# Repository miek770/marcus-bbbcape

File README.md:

# marcus-bbbcape

Beaglebone Black cape for my robot, see:

- [marcus-base](https://github.com/miek770/marcus-base)
- [marcus-boucliers](https://github.com/miek770/marcus-boucliers)

The general goal is to reduce the amount of loose wires on the robot and the required space. The current platform is not compact at all, and adding more stuff (ex.: cannon, turrent, shields) seems like quite the challenge.

Ideally I would use Molex connectors but it would probably eat up too much space. I would like to keep the PCB as small as possible, mostly to keep the cost down. Right-angle headers would work as well, but I think I'll quickly run out of borders. Perhaps right-angle headers for stuff going down, and straight headers for stuff going up?

The cape should be stackable, which means that P8 and P9 should be female headers with long leads. The alternative would be male headers mounted on the bottom. Then again, with plenty of headers going up I probably won't be able to put another cape on top anyways. Still, having female headers allows me to add wires in the future for unplanned expansions.

## 1. To do list

- Add UART2;
- Add battery voltage monitoring (remember the 1.8V analog input limitation);
- Move the top headers' titles below them, otherwise they will be hidden by the right-angle headers I plan on using;
- Correct title, it's partially hidden by the P9 header;
- Output 6.5V somewhere other than for the camera. Some other system may very well need it;
- I don't like how the rangefinders' pins are mirrored, but I've added indications. If it's not too complicated I'd like to mirror 2 of them;
- Add an LED tied to an unused pin, for testing purposes;
- Double-check the big capacitor polarity. I would've thought the square pad to be for the negative pin, but the top silk screen says otherwise;
- Add headers 1st pin markers on all of them and resize the existing 1's (not existing ones but existing 1's);
- Document pins usage. Just need to integrate this info in marcus-base/modules/pins.py which holds a dictionary of pins usage.

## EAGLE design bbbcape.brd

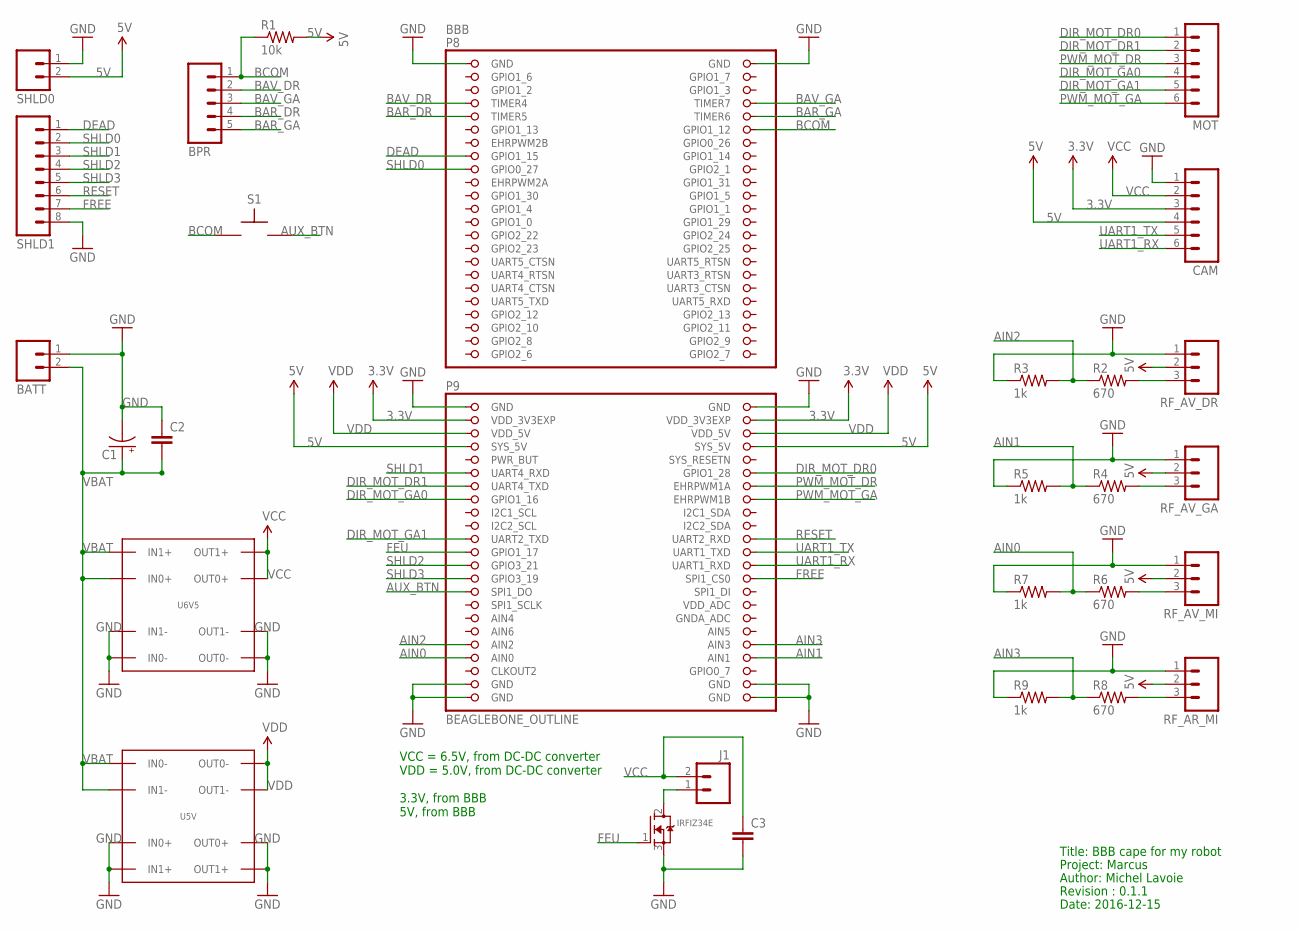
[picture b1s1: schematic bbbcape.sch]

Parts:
BATT: M02PTH; 1X02
BBB: BEAGLEBONE_OUTLINE; BEAGLEBONE_SHIELD
BPR: M05PTH; 1X05
C1: 100UF-25V-20%(PTH); CPOL-RADIAL-100UF-25V
C2, C3: 0.1UF-50V-20%(PTH)KIT-EZ; CAP-PTH-SMALL-KIT
CAM: M06SILK_FEMALE_PTH; 1X06
IRFIZ34E: MOSFET-NGDS_TO220V; TO220V
J1: M02PTH; 1X02
MOT: M06SILK_FEMALE_PTH; 1X06
R1: 10k; AXIAL-0.3
R2, R4, R6, R8: 670; AXIAL-0.3
R3, R5, R7, R9: 1k; AXIAL-0.3
RF_AR_MI: M03PTH; 1X03
RF_AV_DR: M03PTH; 1X03
RF_AV_GA: M03PTH; 1X03
RF_AV_MI: M03PTH; 1X03
S1: TACTILE-SPST-6MM-SLIM; 6MM-SLIM
SHLD0: M02PTH; 1X02
SHLD1: M08; 1X08_ROUND
U5V, U6V5: SEEED-MP1584

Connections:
3.3V: BBB.49 (VDD_3V3EXP), BBB.50 (VDD_3V3EXP), CAM.3
5V: BBB.53 (SYS_5V), BBB.54 (SYS_5V), CAM.4, R1.P$2 (2), RF_AR_MI.2, RF_AV_DR.2, RF_AV_GA.2, RF_AV_MI.2, SHLD0.2
AIN0: BBB.85 (AIN0), R6.P$1 (1), R7.P$2 (2)
AIN1: BBB.86 (AIN1), R4.P$1 (1), R5.P$2 (2)
AIN2: BBB.83 (AIN2), R2.P$1 (1), R3.P$2 (2)
AIN3: BBB.84 (AIN3), R8.P$1 (1), R9.P$2 (2)
AUX_BTN: BBB.75 (SPI1_DO), S1.P$2
BAR_DR: BBB.9 (TIMER5), BPR.4
BAR_GA: BBB.10 (TIMER6), BPR.5
BAV_DR: BBB.7 (TIMER4), BPR.2
BAV_GA: BBB.8 (TIMER7), BPR.3
BCOM: BBB.12 (GPIO1_12), BPR.1, R1.P$1 (1), S1.P$1
DEAD: BBB.15 (GPIO1_15), SHLD1.1
DIR_MOT_DR0: BBB.58 (GPIO1_28), MOT.1
DIR_MOT_DR1: BBB.59 (UART4_TXD), MOT.2
DIR_MOT_GA0: BBB.61 (GPIO1_16), MOT.4
DIR_MOT_GA1: BBB.67 (UART2_TXD), MOT.5
FEU: BBB.69 (GPIO1_17), IRFIZ34E.1 (G)
FREE: BBB.74 (SPI1_CS0), SHLD1.7
GND: BATT.1, BBB.1 (GND), BBB.2 (GND), BBB.47 (GND), BBB.48 (GND), BBB.89 (GND), BBB.90 (GND), BBB.91 (GND), BBB.92 (GND), C1.2 (-), C2.1, C3.2, CAM.1, IRFIZ34E.3 (S), R3.P$1 (1), R5.P$1 (1), R7.P$1 (1), R9.P$1 (1), RF_AR_MI.1, RF_AV_DR.1, RF_AV_GA.1, RF_AV_MI.1, SHLD0.1, SHLD1.8, U5V.IN0+, U5V.IN1+, U5V.OUT0+, U5V.OUT1+, U6V5.IN0-, U6V5.IN1-, U6V5.OUT0-, U6V5.OUT1-
unnamed: R2.P$2 (2), RF_AV_DR.3
unnamed: R4.P$2 (2), RF_AV_GA.3
unnamed: IRFIZ34E.2 (D), J1.1
unnamed: R6.P$2 (2), RF_AV_MI.3
unnamed: R8.P$2 (2), RF_AR_MI.3
PWM_MOT_DR: BBB.60 (EHRPWM1A), MOT.3
PWM_MOT_GA: BBB.62 (EHRPWM1B), MOT.6
RESET: BBB.68 (UART2_RXD), SHLD1.6
SHLD0: BBB.17 (GPIO0_27), SHLD1.2
SHLD1: BBB.57 (UART4_RXD), SHLD1.3
SHLD2: BBB.71 (GPIO3_21), SHLD1.4
SHLD3: BBB.73 (GPIO3_19), SHLD1.5
UART1_RX: BBB.72 (UART1_RXD), CAM.6
UART1_TX: BBB.70 (UART1_TXD), CAM.5
VBAT: BATT.2, C1.1 (+), C2.2, U5V.IN0-, U5V.IN1-, U6V5.IN0+, U6V5.IN1+
VCC: C3.1, CAM.2, J1.2, U6V5.OUT0+, U6V5.OUT1+
VDD: BBB.51 (VDD_5V), BBB.52 (VDD_5V), U5V.OUT0-, U5V.OUT1-

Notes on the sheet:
Title: BBB cape for my robot
Project: Marcus
Author: Michel Lavoie
Revision : 0.1.1
Date: 2016-12-15
VCC = 6.5V, from DC-DC converter VDD = 5.0V, from DC-DC converter 3.3V, from BBB 5V, from BBB

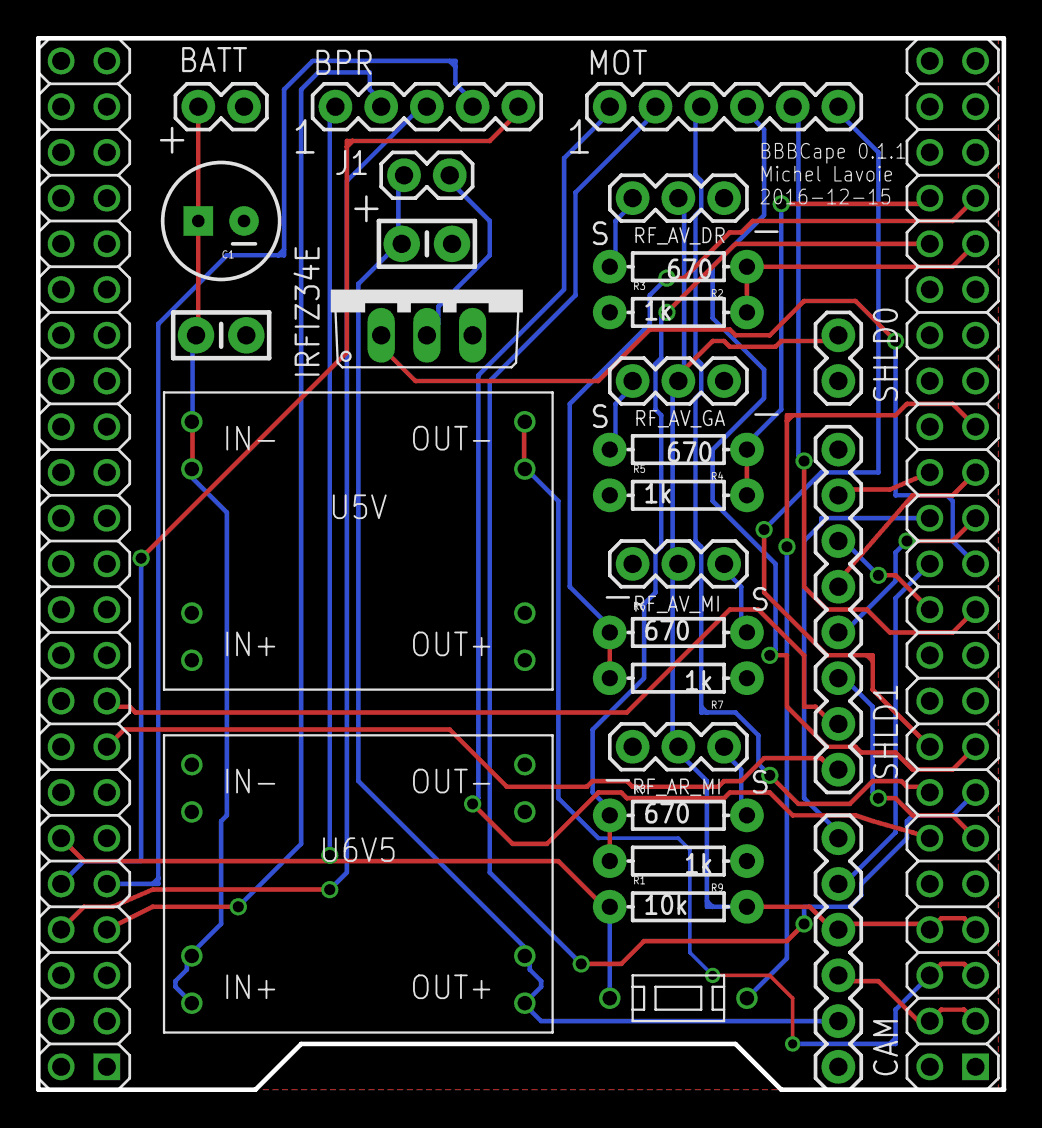
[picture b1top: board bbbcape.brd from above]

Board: 2 copper layers, 53.7 x 58.4 mm, 28 parts (0 on the bottom side), 37 nets.

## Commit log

2016-12-11 Started schematic and to do list.
2016-12-11 Added links
2016-12-11 New item in to do list.
2016-12-11 Connected motors.
2016-12-11 Connected CMUCam2+.
2016-12-11 Connected bumpers.
2016-12-11 Added frame.
2016-12-11 Connected GP2D12 rangefinders.
2016-12-11 Separated VDD_5V and SYS_5V, per manual.
2016-12-11 Connected shields.
2016-12-11 Added and connected firing circuit.
2016-12-11 Added reset button (on BAR_GA, P8_10).
2016-12-11 Replaced S1
2016-12-11 Added description.
2016-12-11 Added more thoughts.
2016-12-11 Added item in to do list.
2016-12-13 Added schematic image.
2016-12-16 Added new DC-DC converter symbol (instead of headers).
2016-12-16 Switched a few pins to confirmed useable pins.
2016-12-16 PCB done.
2016-12-16 Generated images, but there's an error with the layout.
2016-12-16 Trying to reduce the board overall dimensions, no success...
2016-12-16 Board outline is now fine.
2016-12-16 Added notes for version 0.1.2, before ordering the PCB.
2016-12-25 Updated To Do List.

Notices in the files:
parts and their libraries:
SparkFun-Connectors: Licensing: Creative Commons ShareAlike 4.0 International - https://creativecommons.org/licenses/by-sa/4.0
